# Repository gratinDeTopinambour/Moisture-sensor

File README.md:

# 🌿 Capacitive Soil Moisture Sensor

A complete **open-source capacitive soil moisture sensor project** based on the **STM32U073CB** microcontroller.

This repository contains all resources for the project:
* 📐 **3D Design**: Modular enclosure for 3D printing.
* 🔌 **Electronics (V1 & V2)**: KiCad files, Gerbers, BOM, PDF schematics, and 3D models.
* 💻 **Firmware**: C/C++ source code optimized for STM32 (STM32CubeIDE / STM32CubeMX project).
* 📖 **Documentation**: User manual and component datasheets.

---

## 🖼️ Project Overview

| Complete Enclosure | Assembled PCB |
| :---: | :---: |
|  |  |

---

## 📂 Project Structure

```text
Moisture-sensor/
├── 3D_design/                             # CAD files for 3D printing
│   ├── moisture_sensor_capot.3mf         # Main top cover (3MF)
│   ├── moisture_sensor_capot_ecran.stl   # Top cover with display cutout (STL)
│   └── moisture_sensor_capot_pile.stl    # Battery hatch / compartment (STL)
│
├── Electronics/                           # Electronics design files
│   ├── datasheet/                         # Component datasheets
│   ├── Moisture_sensorV1/                 # First revision
│   └── Moisture_sensorV2/                 # Revision V2 (Main)
│       ├── 3D_model/                      # Complete PCB 3D STEP model
│       ├── BOM/                           # Bill of Materials (BOM)
│       ├── gerber_file/                   # Gerber files for PCB manufacturing
│       ├── KICAD/                         # KiCad CAD project (Schematics + PCB)
│       └── pdf_version/                   # Schematics in PDF format
│
├── Program/                               # Firmware & Source code
│   └── STM32U073CB/                       # STM32CubeIDE / CubeMX project
│       ├── Core/                          # Application source code (Inc, Src, Main)
│       ├── Drivers/                       # STM32 HAL and CMSIS drivers
│       ├── Capacitive_Moisture_sensor.ioc # STM32CubeMX configuration
│       ├── Capacitive_Moisture_sensor Debug.launch # Debug launch configuration
│       └── STM32U073CBTX_FLASH.ld         # Flash linker script
│
├── pictures/                              # Project pictures
│   ├── moisture_sensor.jpg
│   └── populated_PCB.jpg
│
├── Moisture_sensor_User_Manual.pdf        # Complete user manual (PDF)
├── Moisture_sensor_User_Manual.odt        # Editable user manual (ODT)
└── README.md                              # Main repository documentation

---

## ⚡ Technical Specifications

* **Microcontroller**: STM32U073CB (Ultra-low-power ARM Cortex-M0+).
* **Measurement Technology**: Capacitive (corrosion-resistant compared to resistive sensors).
* **PCB Design**: Designed with **KiCad** (V2 revision available with production-ready Gerber files).
* **Power Supply**: Designed for battery operation with a quick-access hatch.
* **Display (Optional)**: Screen support using the custom top cover.

---

## 🖨️ 3D Printed Enclosure

Parts are located in the `3D_design/` directory.

| Part | Format | Description |
| :--- | :--- | :--- |
| `moisture_sensor_capot.3mf` | `.3mf` | Standard solid top cover |
| `moisture_sensor_capot_ecran.stl` | `.stl` | Top cover with cutout for display integration |
| `moisture_sensor_capot_pile.stl` | `.stl` | Battery compartment housing / cover |

---

## 💻 Firmware & Development

Source code is located in `Program/STM32U073CB/`.

### Prerequisites
* [STM32CubeIDE](https://www.st.com/en/development-tools/stm32cubeide.html) (recent version)
* Programmer / Debugger (ST-Link V2 / V3)

### Building and Flashing
1. Open **STM32CubeIDE**.
2. Import the project from `Program/STM32U073CB`.
3. If you wish to modify pinout or peripheral configurations, open `Capacitive_Moisture_sensor.ioc` with STM32CubeMX.
4. Build (`Build Project`) then flash the microcontroller using the included debug configuration (`Capacitive_Moisture_sensor Debug.launch`).

---

## 🏭 PCB Manufacturing (Hardware V2)

To manufacture the V2 PCB:
1. Production-ready manufacturing files (JLCPCB, PCBWay, etc.) are located in `Electronics/Moisture_sensorV2/gerber_file/`.
2. The Bill of Materials (BOM) for soldering is available in `Electronics/Moisture_sensorV2/BOM/`.
3. Schematics can be viewed in KiCad or directly in `Electronics/Moisture_sensorV2/pdf_version/`.

---

## 📖 User Manual

To learn more about calibration, installation, and daily usage of the sensor, refer to:
📄 [Moisture_sensor_User_Manual.pdf](Moisture_sensor_User_Manual.pdf)

---

## 📜 License

This project is released under an open-source license. You are free to use, modify, and distribute it.

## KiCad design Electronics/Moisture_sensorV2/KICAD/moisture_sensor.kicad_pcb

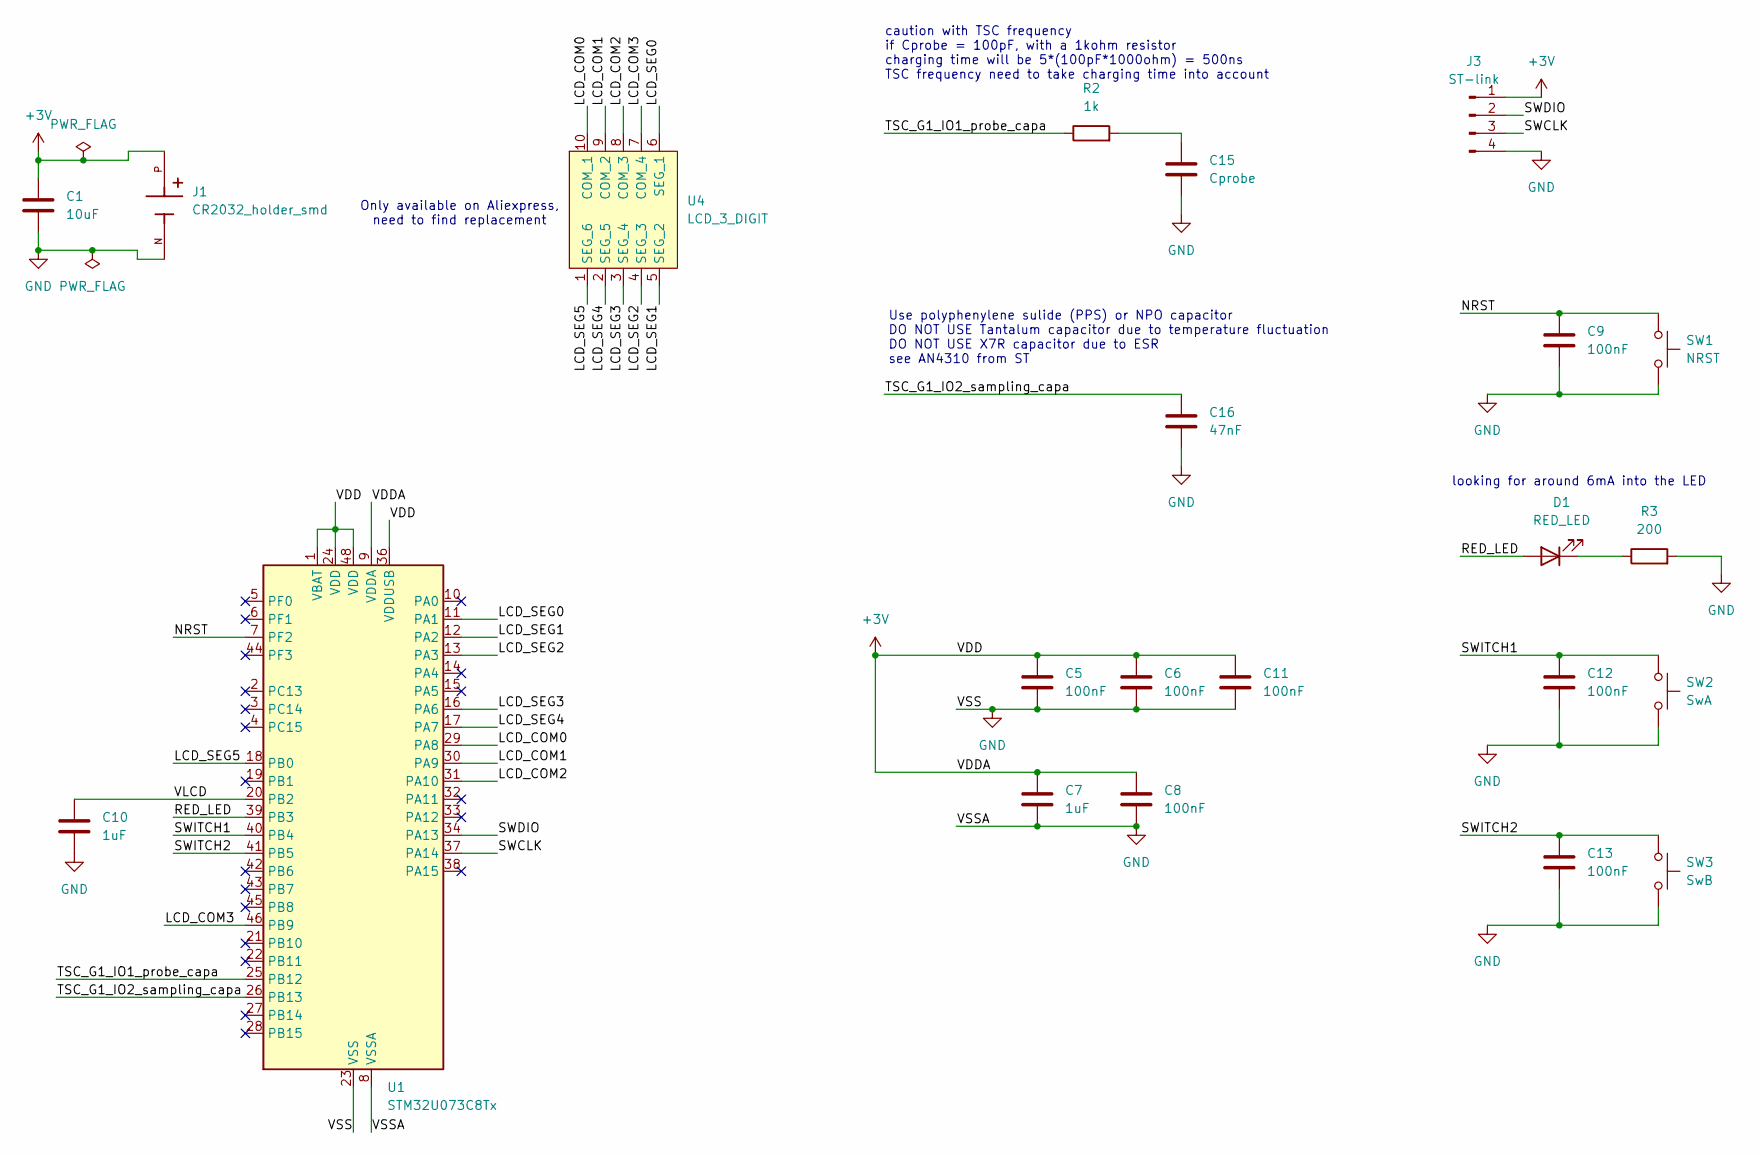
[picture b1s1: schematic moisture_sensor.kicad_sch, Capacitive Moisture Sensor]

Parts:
C1: 10uF; C_0805_2012Metric
C5, C6, C8, C9, C11, C12, C13: 100nF; C_0603_1608Metric
C7, C10: 1uF; C_0603_1608Metric
C15: Cprobe; C_Soil_Moisture_Probe
C16: 47nF; C_1206_3216Metric
D1: RED_LED; LED_0805_2012Metric
J1: CR2032_holder_smd; Porte_Pile_CR2032_smd
J3: ST-link; PinSocket_1x04_P1.27mm_Vertical
R2: 1k; R_0603_1608Metric
R3: 200; R_0603_1608Metric
SW1: NRST; SW_Push_1P1T_NO_Vertical_Wuerth_434133025816
SW2: SwA; SW_Push_1P1T_NO_Vertical_Wuerth_434133025816
SW3: SwB; SW_Push_1P1T_NO_Vertical_Wuerth_434133025816
U1: STM32U073C8Tx; LQFP-48_7x7mm_P0.5mm
U4: LCD_3_DIGIT; LCD_DISPLAY_THT_10PIN

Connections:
+3V: C1.1, C5.1, C6.1, C7.1, C8.1, C11.1, J1.P, J3.1, U1.1 (VBAT), U1.9 (VDDA), U1.24 (VDD), U1.36 (VDDUSB), U1.48 (VDD)
/LCD_COM0: U1.29 (PA8), U4.10 (COM_1)
/LCD_COM1: U1.30 (PA9), U4.9 (COM_2)
/LCD_COM2: U1.31 (PA10), U4.8 (COM_3)
/LCD_COM3: U1.46 (PB9), U4.7 (COM_4)
/LCD_SEG0: U1.11 (PA1), U4.6 (SEG_1)
/LCD_SEG1: U1.12 (PA2), U4.5 (SEG_2)
/LCD_SEG2: U1.13 (PA3), U4.4 (SEG_3)
/LCD_SEG3: U1.16 (PA6), U4.3 (SEG_4)
/LCD_SEG4: U1.17 (PA7), U4.2 (SEG_5)
/LCD_SEG5: U1.18 (PB0), U4.1 (SEG_6)
/NRST: C9.1, SW1.1, U1.7 (PF2)
/RED_LED: D1.2 (A), U1.39 (PB3)
/SWCLK: J3.3, U1.37 (PA14)
/SWDIO: J3.2, U1.34 (PA13)
/SWITCH1: C12.1, SW2.1, U1.40 (PB4)
/SWITCH2: C13.1, SW3.1, U1.41 (PB5)
/TSC_G1_IO1_probe_capa: R2.1, U1.25 (PB12)
/TSC_G1_IO2_sampling_capa: C16.1, U1.26 (PB13)
/VLCD: C10.1, U1.20 (PB2)
GND: C1.2, C5.2, C6.2, C7.2, C8.2, C9.2, C10.2, C11.2, C12.2, C13.2, C15.2, C16.2, J1.N, J3.4, R3.2, SW1.2, SW2.2, SW3.2, U1.8 (VSSA), U1.23 (VSS), U1.35 (VSS), U1.47 (VSS)
unnamed: C15.1, R2.2
unnamed: D1.1 (K), R3.1

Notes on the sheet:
Use polyphenylene sulide (PPS) or NPO capacitor DO NOT USE Tantalum capacitor due to temperature fluctuation DO NOT USE X7R capacitor due to ESR see AN4310 from ST
Only available on Aliexpress, need to find replacement
caution with TSC frequency if Cprobe = 100pF, with a 1kohm resistor charging time will be 5*(100pF*1000ohm) = 500ns TSC frequency need to take charging time into account
looking for around 6mA into the LED

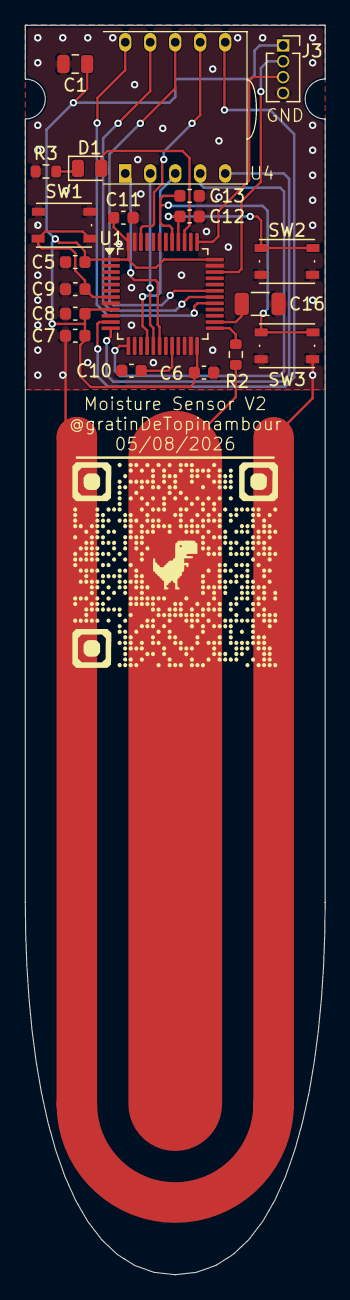
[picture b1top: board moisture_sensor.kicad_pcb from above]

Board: 2 copper layers, 24.0 x 100.0 mm, 22 parts (1 on the bottom side), 23 nets.

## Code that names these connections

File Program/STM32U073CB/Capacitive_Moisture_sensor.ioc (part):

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Mcu.Name=STM32U073CBTx
Mcu.Package=LQFP48
Mcu.UserName=STM32U073CBTx
PA1.Mode=SEG0
PA1.Signal=LCD_SEG0
PA10.Mode=1/4 Duty Cycle
PA10.Signal=LCD_COM2
PA2.Mode=SEG1
PA2.Signal=LCD_SEG1
PA3.Mode=SEG2
PA3.Signal=LCD_SEG2
PA6.Mode=SEG3
PA6.Signal=LCD_SEG3
PA7.Mode=SEG4
PA7.Signal=LCD_SEG4
PA8.Mode=1/4 Duty Cycle
PA8.Signal=LCD_COM0
PA9.Mode=1/4 Duty Cycle
PA9.Signal=LCD_COM1
PB0.Mode=SEG5
PB0.Signal=LCD_SEG5
PB12.GPIOParameters=GPIO_Label
PB12.GPIO_Label=Probe_Capa
PB12.Mode=G1_IO1-Channel
PB12.Signal=TSC_G1_IO1
PB13.GPIOParameters=GPIO_Label
PB13.GPIO_Label=Sampling_Capa
PB13.Mode=G1_IO2-Sampling
PB13.Signal=TSC_G1_IO2
PB2.Mode=1/4 Duty Cycle
PB2.Signal=LCD_VLCD
PB3.GPIOParameters=GPIO_Label
PB3.GPIO_Label=RED_LED
PB3.Signal=GPIO_Output
PB4.GPIOParameters=GPIO_PuPd,GPIO_Label,GPIO_ModeDefaultEXTI
PB4.GPIO_Label=CAL_SW
PB4.GPIO_ModeDefaultEXTI=GPIO_MODE_IT_FALLING
PB4.GPIO_PuPd=GPIO_PULLUP
PB4.Signal=GPXTI4
PB5.GPIOParameters=GPIO_PuPd,GPIO_Label,GPIO_ModeDefaultEXTI
PB5.GPIO_Label=MES_SW
PB5.GPIO_ModeDefaultEXTI=GPIO_MODE_IT_FALLING
PB5.GPIO_PuPd=GPIO_PULLUP
PB5.Signal=GPXTI5
PB9.Mode=1/4 Duty Cycle
PB9.Signal=LCD_COM3
RCC.HSE_VALUE=4000000
RCC.SYSCLKFreq_VALUE=16000000
board=custom
